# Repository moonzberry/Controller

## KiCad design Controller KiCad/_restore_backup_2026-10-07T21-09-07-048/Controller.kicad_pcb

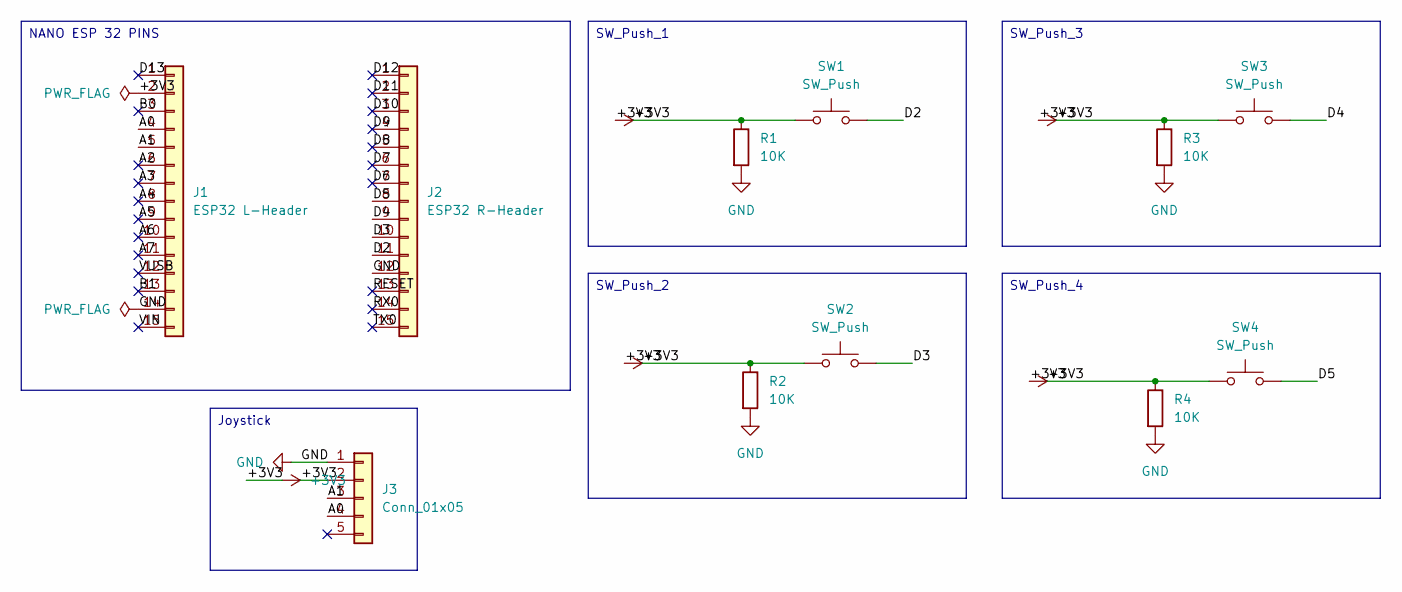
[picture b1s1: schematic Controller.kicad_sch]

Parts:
J1: ESP32 L-Header; PinHeader_1x15_P2.54mm_Vertical
J2: ESP32 R-Header; PinHeader_1x15_P2.54mm_Vertical
J3: Conn_01x05; PinHeader_1x05_P2.54mm_Vertical
R1, R2, R3, R4: 10K; R_Axial_DIN0207_L6.3mm_D2.5mm_P7.62mm_Horizontal
SW1, SW2, SW3, SW4: SW_Push; SW_PUSH_6mm

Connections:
+3V3: J1.2, J3.2, R1.1, R2.1, R3.1, R4.1, SW1.1, SW2.1, SW3.1, SW4.1
/A0: J1.4, J3.4
/A1: J1.5, J3.3
/A2: J1.6
/A3: J1.7
/A4: J1.8
/A5: J1.9
/A6: J1.10
/A7: J1.11
/B0: J1.3
/B1: J1.13
/D2: J2.11, SW1.2
/D3: J2.10, SW2.2
/D4: J2.9, SW3.2
/D5: J2.8, SW4.2
/D6: J2.7
/D7: J2.6
/D8: J2.5
/D9: J2.4
/D10: J2.3
/D11: J2.2
/D12: J2.1
/D13: J1.1
/RESET: J2.13
/RX0: J2.14
/TX0: J2.15
/VIN: J1.15
/VUSB: J1.12
GND: J1.14, J2.12, J3.1, R1.2, R2.2, R3.2, R4.2

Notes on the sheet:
SW_Push_4
SW_Push_1
NANO ESP 32 PINS
SW_Push_3
Joystick
SW_Push_2

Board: 2 copper layers, 11 parts (0 on the bottom side), 8 nets, no tracks yet.
